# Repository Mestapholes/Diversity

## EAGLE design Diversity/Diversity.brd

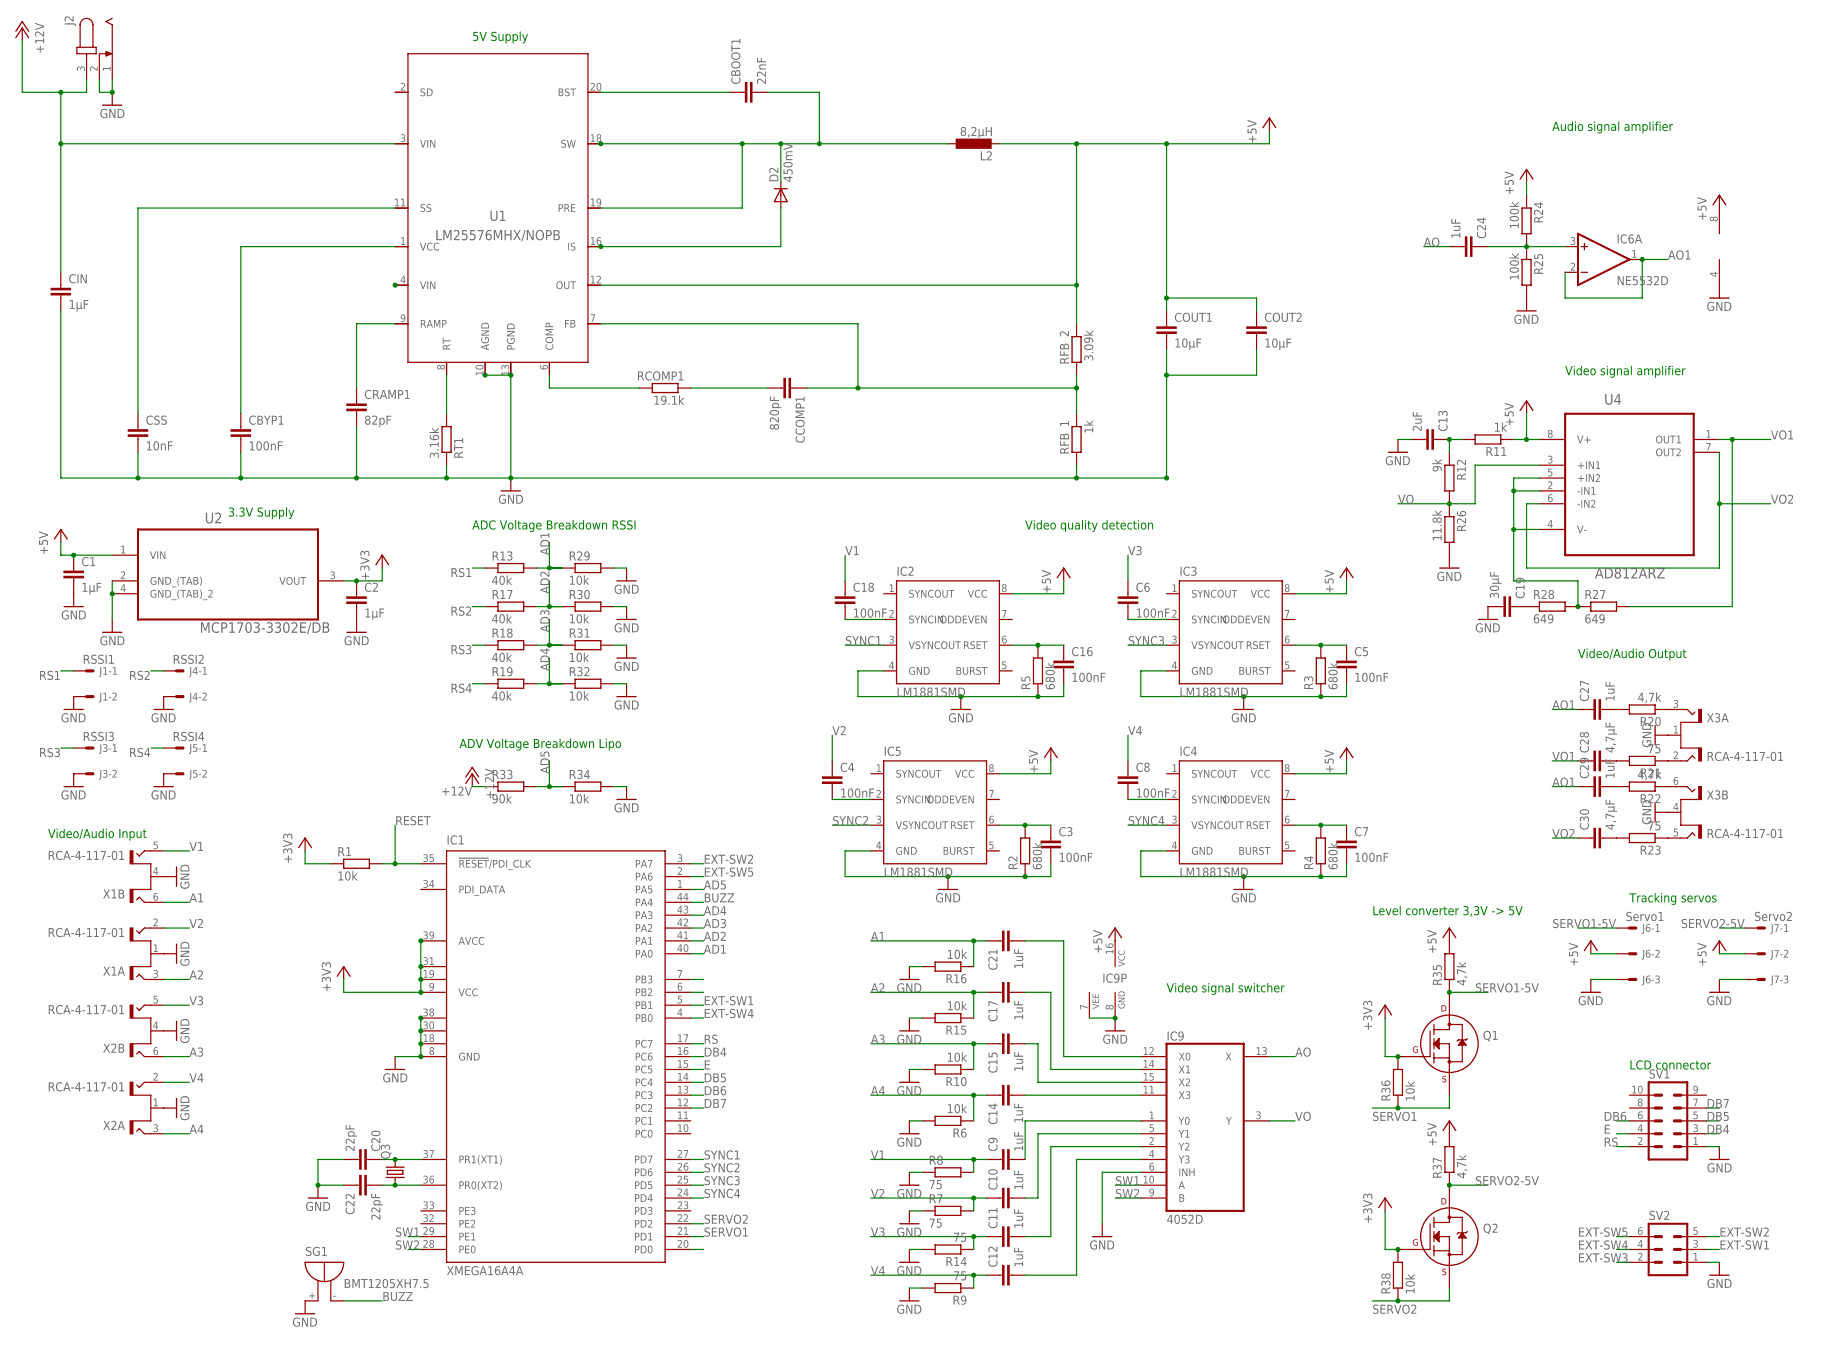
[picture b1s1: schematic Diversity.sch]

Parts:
C1, C2: 1µF; C0805
C3, C4, C5, C6, C7, C8, C16, C18: 100nF; C0805
C9, C10, C11, C12, C14, C15, C17, C21, C24, C27, C29: 1uF; C0805
C13: 2uF; C0805
C19: 30µF; C0805
C20, C22: 22pF; C0805
C28, C30: 4,7µF; C0805
CBOOT1: 22nF; C0805
CBYP1: 100nF; C0805
CCOMP1: 820pF; C0805
CIN: 1µF; C0805
COUT1, COUT2: 10µF; C0805
CRAMP1: 82pF; C0805
CSS: 10nF; C0805
D2: 450mV; DO214AC
IC1: XMEGA16A4A; TQFP44
IC2, IC3, IC4, IC5: LM1881SMD; SOIC08
IC6: NE5532D; SO08
IC9: 4052D; SO16
J1: RSSI1; 7395-02
J2: JACK-PLUG0; SPC4077
J3: RSSI3; 7395-02
J4: RSSI2; 7395-02
J5: RSSI4; 7395-02
J6: Servo1; 7395-03
J7: Servo2; 7395-03
L2: 8,2µH; FPS
Q1, Q2: 2N7002_SOT23; SOT-23
Q3: CRYSTALHC49UP; HC49UP
R1, R29, R30, R31, R32, R34: 10k; R0805@1
R2, R3, R4, R5: 680k; R0805
R6, R10, R15, R16: 10k; M0805
R7, R8, R9, R14: 75; M0805
R11: 1k; R0805
R12: 9k; R0805
R13, R17, R18, R19: 40k; R0805@1
R20, R22, R35, R37: 4,7k; R0805
R21, R23: 75; R0805
R24, R25: 100k; R0805
R26: 11.8k; R0805
R27, R28: 649; R0805
R33: 90k; R0805@1
R36, R38: 10k; R0805
RCOMP1: 19.1k; R0805
RFB_1: 1k; R0805
RFB_2: 3.09k; R0805
RT1: 3.16k; R0805
SG1: BMT1205XH7.5
SV1: ML10
SV2: ML6
U1: LM25576MHX/NOPB; MXA20A
U2: MCP1703-3302E/DB; SOT230P700X180-4N
U4: AD812ARZ; SOIC127P600X175-8N
X1, X2, X3: RCA-4-117-01

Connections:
1: CSS.1, U1.11 (SS)
2: CBYP1.1, U1.1 (VCC)
3: CRAMP1.1, U1.9 (RAMP)
5: RCOMP1.2, U1.6 (COMP)
6: CCOMP1.1, RFB_1.1, RFB_2.2, U1.7 (FB)
7: CBOOT1.2, D2.C, L2.P$1 (1), U1.17 (SW), U1.18 (SW), U1.19 (PRE)
8: D2.A, U1.15 (IS), U1.16 (IS)
11: CBOOT1.1, U1.20 (BST)
12: CCOMP1.2, RCOMP1.1
+3V3: C2.1, IC1.9 (VCC), IC1.19 (VCC1), IC1.31 (VCC2), IC1.39 (AVCC), Q1.1 (G), Q2.1 (G), R1.1, R36.2, R38.2, U2.3 (VOUT)
+5V: C1.1, COUT1.1, COUT2.1, IC2.8 (VCC), IC3.8 (VCC), IC4.8 (VCC), IC5.8 (VCC), IC6.8 (V+), IC9.16 (VCC), J6.2, J7.2, L2.P$2 (2), R11.1, R24.1, R35.2, R37.2, RFB_2.1, U1.12 (OUT), U2.1 (VIN), U4.8 (V+)
+12V: CIN.1, J2.3, R33.1, U1.3 (VIN)
A1: C21.1, R16.1, X1.6 (T2)
A2: C17.1, R15.1, X1.3 (T2)
A3: C15.1, R10.1, X2.6 (T2)
A4: C14.1, R6.1, X2.3 (T2)
AD1: IC1.40 (PA0), R13.2, R29.1
AD2: IC1.41 (PA1), R17.2, R30.1
AD3: IC1.42 (PA2), R18.2, R31.1
AD4: IC1.43 (PA3), R19.2, R32.1
AD5: IC1.1 (PA5), R33.2, R34.1
AO: C24.2, IC9.13 (X)
AO1: C27.1, C29.1, IC6.1 (OUT), IC6.2 (-IN)
BUZZ: IC1.44 (PA4), SG1.-
DB4: IC1.16 (PC6), SV1.3
DB5: IC1.14 (PC4), SV1.5
DB6: IC1.13 (PC3), SV1.6
DB7: IC1.12 (PC2), SV1.7
E: IC1.15 (PC5), SV1.4
EXT-SW1: IC1.5 (PB1), SV2.3
EXT-SW2: IC1.3 (PA7), SV2.5
EXT-SW3: IC1.6 (PB2), SV2.2
EXT-SW4: IC1.4 (PB0), SV2.4
EXT-SW5: IC1.2 (PA6), SV2.6
GND: C1.2, C2.2, C13.2, C19.2, C20.2, C22.1, CBYP1.2, CIN.2, COUT1.2, COUT2.2, CRAMP1.2, CSS.2, IC1.8 (GND), IC1.18 (GND1), IC1.30 (GND2), IC1.38 (GND3), IC6.4 (V-), IC9.6 (INH), IC9.7 (VEE), IC9.8 (GND), J1.2, J2.1, J2.2, J3.2, J4.2, J5.2, J6.3, J7.3, R6.2, R7.1, R8.1, R9.2, R10.2, R14.2, R15.2, R16.2, R25.2, R26.2, R29.2, R30.2, R31.2, R32.2, R34.2, RFB_1.2, RT1.1, SG1.+, SV1.1, SV2.1, U1.10 (AGND), U1.13 (PGND), U1.14 (PGND), U1.21 (DAP), U2.2 (GND_(TAB)), U2.4 (GND_(TAB)_2), X1.1 (S), X1.4 (S), X2.1 (S), X2.4 (S), X3.1 (S), X3.4 (S)
GND1: C3.2, C5.2, C7.2, C16.2, IC2.4 (GND), IC3.4 (GND), IC4.4 (GND), IC5.4 (GND), R2.1, R3.1, R4.1, R5.1
unnamed: U1.4 (VIN), U1.5 (SYNC)
unnamed: RT1.2, U1.8 (RT)
unnamed: C20.1, IC1.37 (PR1(XT1)), Q3.2
unnamed: C3.1, IC5.6 (RSET), R2.2
unnamed: C4.2, IC5.2 (SYNCIN)
unnamed: C5.1, IC3.6 (RSET), R3.2
unnamed: C6.2, IC3.2 (SYNCIN)
unnamed: C7.1, IC4.6 (RSET), R4.2
unnamed: C8.2, IC4.2 (SYNCIN)
unnamed: C15.2, IC9.15 (X2)
unnamed: C17.2, IC9.14 (X1)
unnamed: C9.2, IC9.1 (Y0)
unnamed: C11.2, IC9.2 (Y2)
unnamed: C10.2, IC9.5 (Y1)
unnamed: C21.2, IC9.12 (X0)
unnamed: C22.2, IC1.36 (PR0(XT2)), Q3.1
unnamed: C16.1, IC2.6 (RSET), R5.2
unnamed: C13.1, R11.2, R12.1
unnamed: R27.1, R28.2, U4.2 (-IN1), U4.4 (V-), U4.5 (+IN2)
unnamed: C18.2, IC2.2 (SYNCIN)
unnamed: C19.1, R28.1
unnamed: C12.2, IC9.4 (Y3)
unnamed: C14.2, IC9.11 (X3)
unnamed: R20.1, X3.3 (T2)
unnamed: R21.1, X3.2 (T1)
unnamed: R22.1, X3.6 (T2)
unnamed: R23.1, X3.5 (T1)
unnamed: C27.2, R20.2
unnamed: C28.2, R21.2
unnamed: C29.2, R22.2
unnamed: C30.2, R23.2
unnamed: C24.1, IC6.3 (+IN), R24.2, R25.1
RESET: IC1.35 (!RESET!/PDI_CLK), R1.2
RS: IC1.17 (PC7), SV1.2
RS1: J1.1, R13.1
RS2: J4.1, R17.1
RS3: J3.1, R18.1
RS4: J5.1, R19.1
SERVO1: IC1.21 (PD1), Q1.2 (S), R36.1
SERVO1-5V: J6.1, Q1.3 (D), R35.1
SERVO2: IC1.22 (PD2), Q2.2 (S), R38.1
SERVO2-5V: J7.1, Q2.3 (D), R37.1
SW1: IC1.29 (PE1), IC9.10 (A)
SW2: IC1.28 (PE0), IC9.9 (B)
SYNC1: IC1.27 (PD7), IC2.3 (VSYNCOUT)
SYNC2: IC1.26 (PD6), IC5.3 (VSYNCOUT)
SYNC3: IC1.25 (PD5), IC3.3 (VSYNCOUT)
SYNC4: IC1.24 (PD4), IC4.3 (VSYNCOUT)
V1: C9.1, C18.1, R8.2, X1.5 (T1)
V2: C4.1, C10.1, R7.2, X1.2 (T1)
V3: C6.1, C11.1, R14.1, X2.5 (T1)
V4: C8.1, C12.1, R9.1, X2.2 (T1)
VO: IC9.3 (Y), R12.2, R26.1, U4.3 (+IN1)
VO1: C28.1, R27.2, U4.1 (OUT1)
VO2: C30.1, U4.6 (-IN2), U4.7 (OUT2)

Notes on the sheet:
Video/Audio Input
3.3V Supply
5V Supply
ADC Voltage Breakdown RSSI
Video quality detection
Video signal switcher
Video signal amplifier
Audio signal amplifier
Video/Audio Output
ADV Voltage Breakdown Lipo
Level converter 3,3V -> 5V
Tracking servos
LCD connector

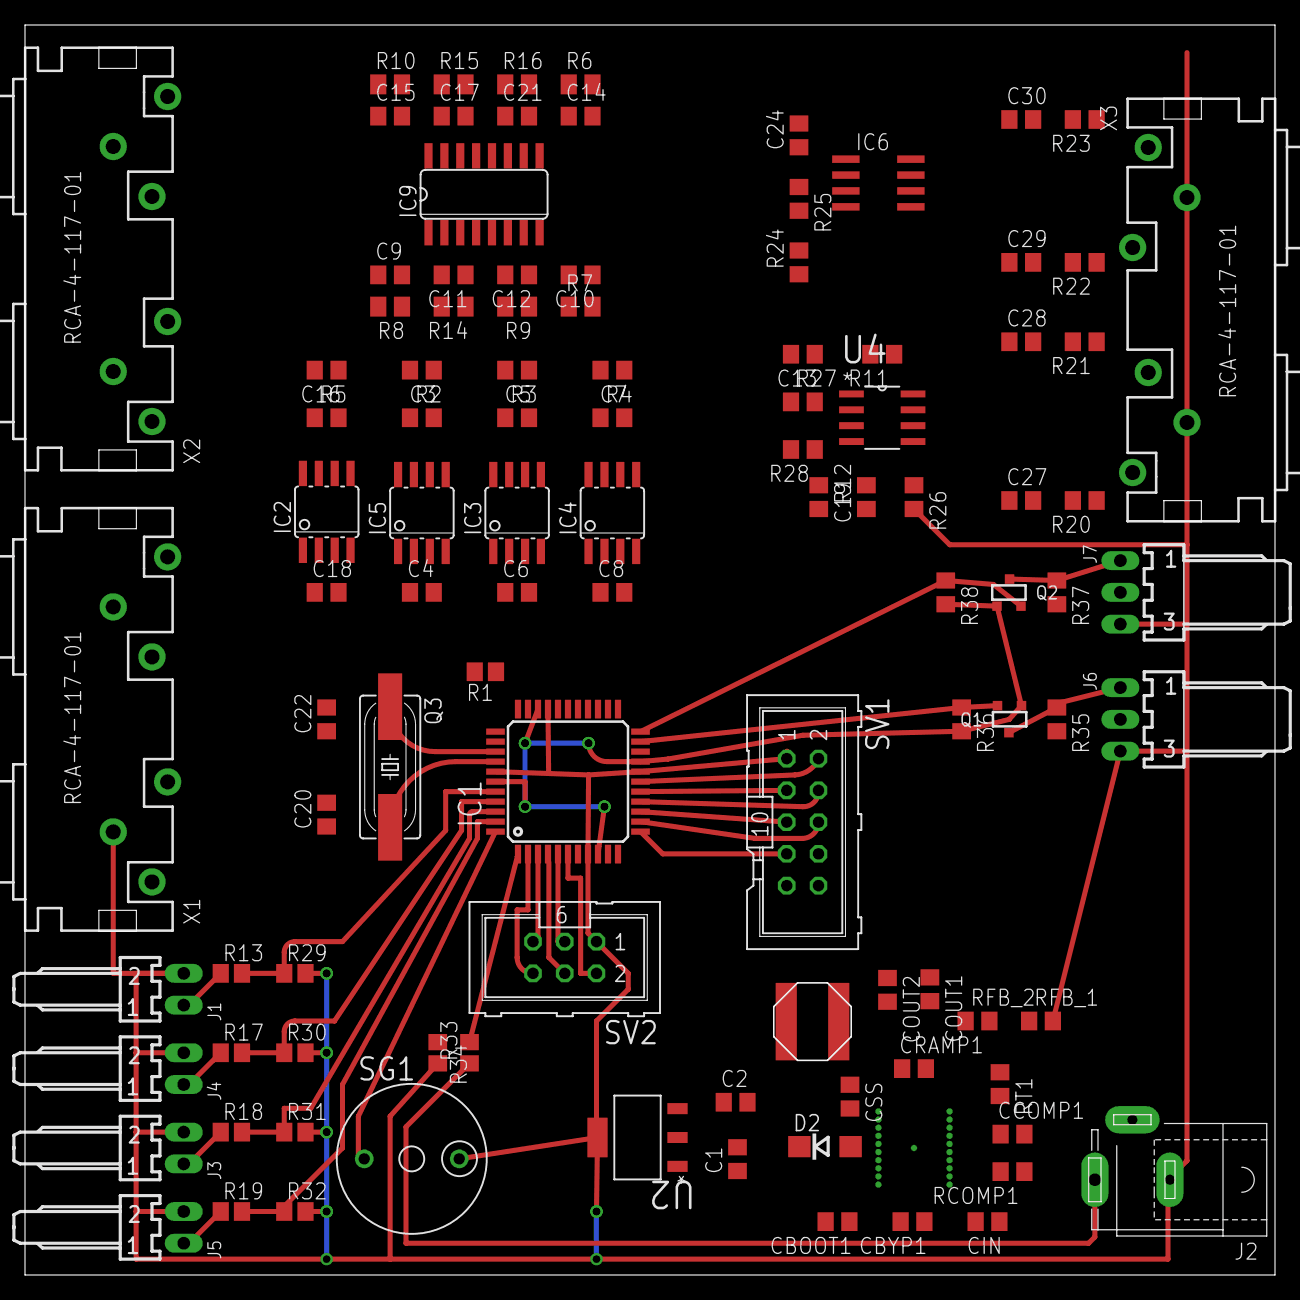
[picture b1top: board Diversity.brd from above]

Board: 2 copper layers, 100.0 x 100.0 mm, 105 parts (0 on the bottom side), 91 nets.

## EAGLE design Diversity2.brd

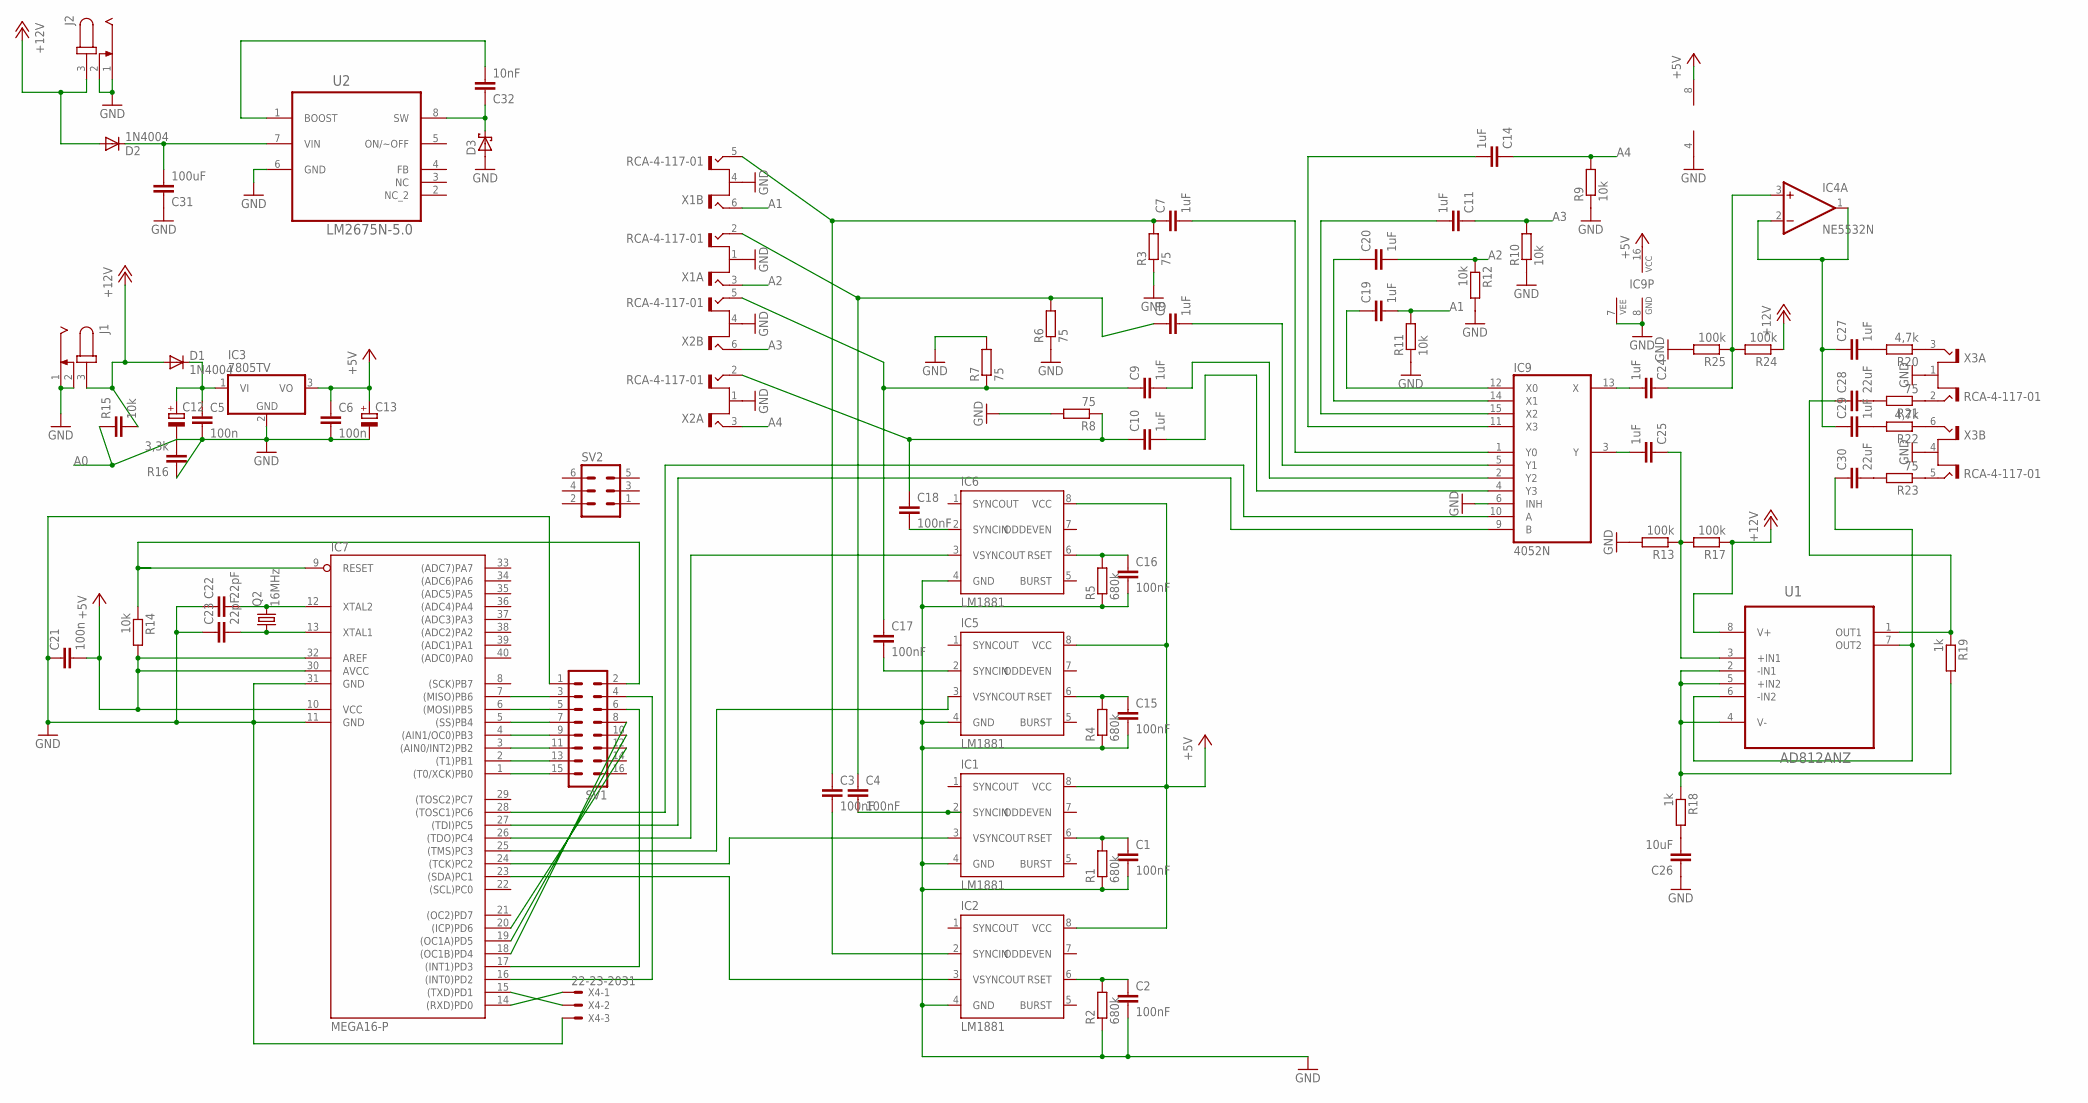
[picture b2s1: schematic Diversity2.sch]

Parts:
C1, C2, C3, C4, C15, C16, C17, C18: 100nF; C2.5-2
C5, C6, C21: 100n; C2.5-2
C7, C8, C9, C10, C11, C14, C19, C20, C24, C25, C27, C29: 1uF; C2.5-2
C12: CPOL-EUE3.5-8; E3,5-8
C13: CPOL-EUE2.5-5; E2,5-5
C22, C23: 22pF; C2.5-2
C26: 10uF; C2.5-2
C28, C30: 22uF; C2.5-2
C31: 100uF; C2.5-2
C32: 10nF; C2.5-2
D1, D2: 1N4004; DO41-10
D3: SCHOTTKY-DIODECB417-15; CB417-15
IC1, IC2, IC5, IC6: LM1881; DIL08
IC3: 7805TV; TO220V
IC4: NE5532N; DIL08
IC7: MEGA16-P; DIL40
IC9: 4052N; DIL16
J1, J2: JACK-PLUG0; SPC4077
Q2: 16MHz; HC49U-V
R1, R2, R4, R5: 680k; 0207/7
R3, R6, R7, R8, R21, R23: 75; 0207/7
R9, R10, R11, R12, R14: 10k; 0207/7
R13, R17, R24, R25: 100k; 0207/7
R15: 10k; C2.5-2
R16: 3,3k; C2.5-2
R18, R19: 1k; 0207/7
R20, R22: 4,7k; 0207/7
SV1: ML16
SV2: ML6L
U1: AD812ANZ; DIP254P762X533-8
U2: LM2675N-5.0; DIP254P762X508-8
X1, X2, X3: RCA-4-117-01
X4: 22-23-2031

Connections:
+5V: C6.1, C13.+, C21.2, IC1.8 (VCC), IC2.8 (VCC), IC3.3 (VO), IC4.8 (V+), IC5.8 (VCC), IC6.8 (VCC), IC7.10 (VCC), IC7.30 (AVCC), IC7.32 (AREF), IC9.16 (VCC), R14.2
+12V: D1.A, D2.A, J1.3, J2.3, R15.2, R17.1, R24.1, U1.8 (V+)
A0: R15.1, R16.2
A1: C19.2, R11.2, X1.6 (T2)
A2: C20.2, R12.1, X1.3 (T2)
A3: C11.1, R10.2, X2.6 (T2)
A4: C14.1, R9.2, X2.3 (T2)
GND: C1.2, C2.2, C5.2, C6.2, C12.-, C13.-, C15.2, C16.2, C21.1, C22.1, C23.1, C26.1, C31.1, D3.A, IC1.4 (GND), IC2.4 (GND), IC3.2 (GND), IC4.4 (V-), IC5.4 (GND), IC6.4 (GND), IC7.11 (GND), IC7.31 (GND), IC9.6 (INH), IC9.7 (VEE), IC9.8 (GND), J1.1, J1.2, J2.1, J2.2, R1.1, R2.1, R3.1, R4.1, R5.1, R6.1, R7.2, R8.2, R9.1, R10.1, R11.1, R12.2, R13.2, R16.1, R25.2, SV1.1, U2.6 (GND), X1.1 (S), X1.4 (S), X2.1 (S), X2.4 (S), X3.1 (S), X3.4 (S), X4.3
unnamed: IC1.3 (VSYNCOUT), IC7.24 ((TCK)PC2)
unnamed: IC2.3 (VSYNCOUT), IC7.23 ((SDA)PC1)
unnamed: C4.1, C8.1, R6.2, X1.2 (T1)
unnamed: C4.2, IC1.2 (SYNCIN)
unnamed: C3.2, IC2.2 (SYNCIN)
unnamed: C7.2, IC9.1 (Y0)
unnamed: C3.1, C7.1, R3.2, X1.5 (T1)
unnamed: C5.1, C12.+, D1.C, IC3.1 (VI)
unnamed: C2.1, IC2.6 (RSET), R2.2
unnamed: C1.1, IC1.6 (RSET), R1.2
unnamed: C8.2, IC9.5 (Y1)
unnamed: C9.2, IC9.2 (Y2)
unnamed: C25.2, IC9.3 (Y)
unnamed: IC5.3 (VSYNCOUT), IC7.25 ((TMS)PC3)
unnamed: IC6.3 (VSYNCOUT), IC7.26 ((TDO)PC4)
unnamed: C11.2, IC9.15 (X2)
unnamed: C16.1, IC6.6 (RSET), R5.2
unnamed: C15.1, IC5.6 (RSET), R4.2
unnamed: C17.2, IC5.2 (SYNCIN)
unnamed: C9.1, C17.1, R7.1, X2.5 (T1)
unnamed: IC7.27 ((TDI)PC5), IC9.9 (B)
unnamed: C18.2, IC6.2 (SYNCIN)
unnamed: C10.1, C18.1, R8.1, X2.2 (T1)
unnamed: IC7.1 ((T0/XCK)PB0), SV1.15
unnamed: C10.2, IC9.4 (Y3)
unnamed: IC7.28 ((TOSC1)PC6), IC9.10 (A)
unnamed: C24.2, IC9.13 (X)
unnamed: C14.2, IC9.11 (X3)
unnamed: C19.1, IC9.12 (X0)
unnamed: C20.1, IC9.14 (X1)
unnamed: C25.1, R13.1, R17.2, U1.3 (+IN1)
unnamed: C26.2, R18.2
unnamed: IC7.9 (RESET), R14.1, SV1.2
unnamed: C23.2, IC7.13 (XTAL1), Q2.1
unnamed: C22.2, IC7.12 (XTAL2), Q2.2
unnamed: R18.1, R19.2, U1.2 (-IN1), U1.4 (V-), U1.5 (+IN2)
unnamed: C28.1, R19.1, U1.1 (OUT1)
unnamed: IC7.2 ((T1)PB1), SV1.13
unnamed: R20.1, X3.3 (T2)
unnamed: R21.1, X3.2 (T1)
unnamed: R22.1, X3.6 (T2)
unnamed: R23.1, X3.5 (T1)
unnamed: C27.2, R20.2
unnamed: C28.2, R21.2
unnamed: C29.2, R22.2
unnamed: C30.2, R23.2
unnamed: C24.1, IC4.3 (+IN), R24.2, R25.1
unnamed: C30.1, U1.6 (-IN2), U1.7 (OUT2)
unnamed: C27.1, C29.1, IC4.1 (OUT), IC4.2 (-IN)
unnamed: IC7.3 ((AIN0/INT2)PB2), SV1.11
unnamed: IC7.4 ((AIN1/OC0)PB3), SV1.9
unnamed: IC7.5 ((SS)PB4), SV1.7
unnamed: IC7.6 ((MOSI)PB5), SV1.5
unnamed: IC7.7 ((MISO)PB6), SV1.3
unnamed: IC7.16 ((INT0)PD2), SV1.4
unnamed: IC7.14 ((RXD)PD0), X4.1
unnamed: IC7.15 ((TXD)PD1), X4.2
unnamed: IC7.17 ((INT1)PD3), SV1.6
unnamed: IC7.18 ((OC1B)PD4), SV1.8
unnamed: IC7.19 ((OC1A)PD5), SV1.10
unnamed: IC7.20 ((ICP)PD6), SV1.12
unnamed: C32.2, U2.1 (BOOST)
unnamed: C31.2, D2.C, U2.7 (VIN)
unnamed: C32.1, D3.C, U2.8 (SW)

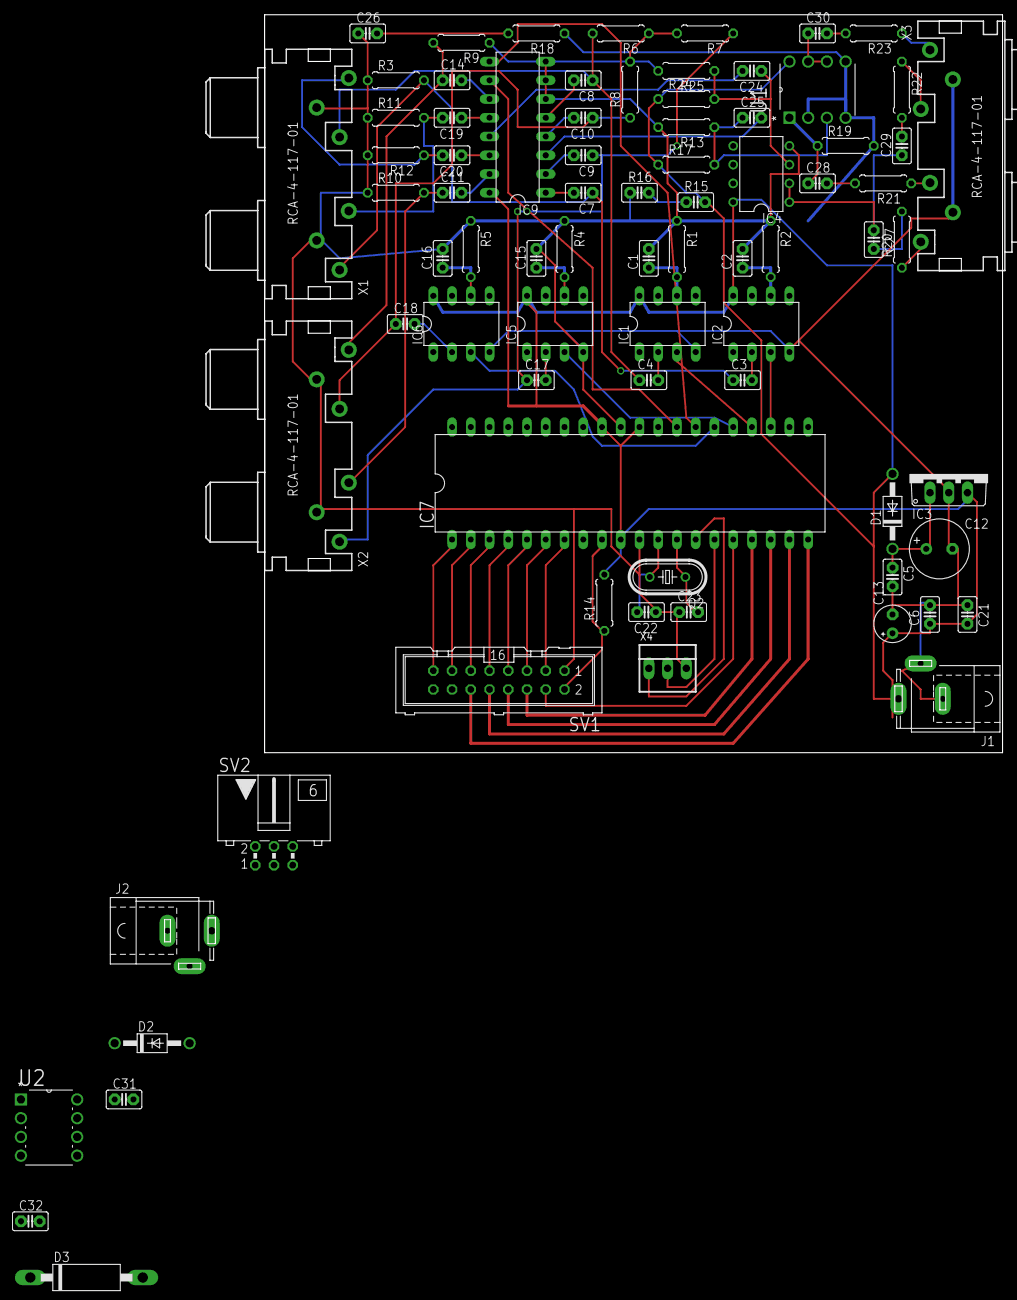
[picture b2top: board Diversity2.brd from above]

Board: 2 copper layers, 100.0 x 100.0 mm, 79 parts (0 on the bottom side), 72 nets.

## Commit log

2014-02-25 Initial
2014-02-25 asdf
2014-02-26 nächster Schritt
2014-02-27 Etwas weitergemacht
2014-02-27 jaja
2014-02-28 noch etwas gefummelt.
2014-03-02 so ist das
2014-03-02 das auch noch
2014-03-03 deleted zip
2014-03-21 Neuer Versuch
